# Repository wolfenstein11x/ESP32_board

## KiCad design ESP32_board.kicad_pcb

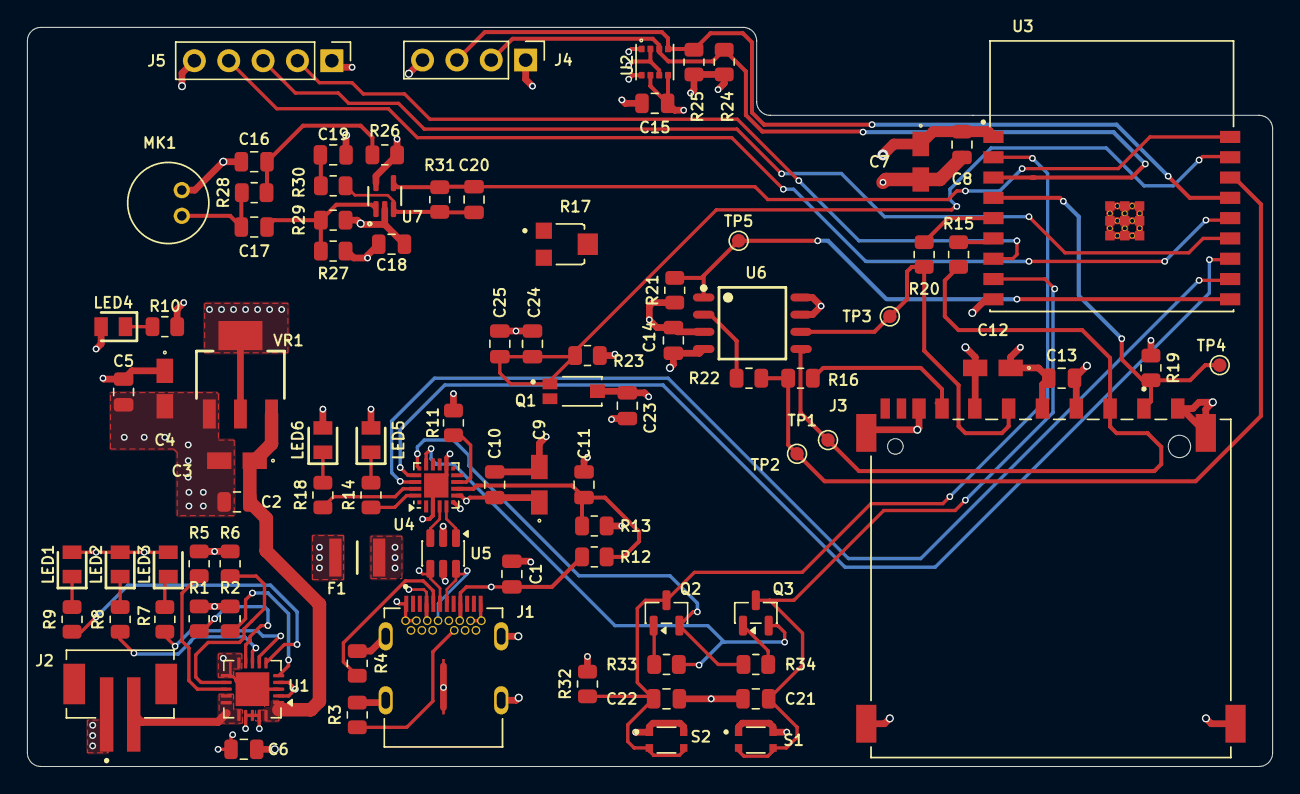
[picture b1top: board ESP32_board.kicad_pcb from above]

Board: 4 copper layers, 92.0 x 54.6 mm, 90 parts (0 on the bottom side), 58 nets.

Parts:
C1, C2, C5, C8, C10, C13, C14, C15, C16, C18, C20, C21, C23: 0.1u; C_0805_2012Metric
C3, C4, C7, C12: 10u; T491A
C6, C11, C19, C22: 1u; C_0805_2012Metric
C9: 4.7u; T491A
C17: 0.01u; C_0805_2012Metric
C24, C25: 10n; C_0805_2012Metric
F1: 0ZCH0110AF2E; FUSC3226X100N
J1: SS-52400-002; BELFUSE_SS-52400-002
J2: B2B-PH-SM4-TB; JST_B2B-PH-SM4-TB
J3: GSD090012SEU; AMPHENOL_GSD090012SEU
J4: Conn_01x04_Pin; PinHeader_1x04_P2.54mm_Vertical
J5: Conn_01x05_Pin; PinHeader_1x05_P2.54mm_Vertical
LED1, LED4, LED6: LTST-C170KRKT; LEDC2012X120N
LED2, LED5: LTST-C170GKT; LEDC2012X120N
LED3: LTST-C170TBKT; LEDC2012X120N
MK1: CMC-5042PF-AC; CUI_CMC-5042PF-AC
Q1: TEMT6000X01; TRANS_TEMT6000X01
Q2, Q3: BC817; SOT-23
R1, R2, R19, R21, R23, R30, R32, R33, R34: 10k; R_0805_2012Metric
R3, R4: 5.1k; R_0805_2012Metric
R5, R26, R28: 2k; R_0805_2012Metric
R6: 20k; R_0805_2012Metric
R7, R8, R9, R10, R14, R18: 470; R_0805_2012Metric
R11: 1k; R_0805_2012Metric
R12: 22.1k; R_0805_2012Metric
R13: 47.5k; R_0805_2012Metric
R15, R16, R20, R22: 50; R_0805_2012Metric
R17: 35WR100KLFTR; TRIM_35WR100KLFTR
R24, R25: 4.7k; R_0805_2012Metric
R27, R29: 1M; R_0805_2012Metric
R31: 100k; R_0805_2012Metric
S1: Boot Button; SW_USLPT2819DT2TR
S2: Reset Button; SW_USLPT2819DT2TR
TP1, TP2, TP3, TP4, TP5: TestPoint; TestPoint_Pad_D1.0mm
U1: MCP73871; QFN-20-1EP_4x4mm_P0.5mm_EP2.5x2.5mm
U2: BME280; PSON65P250X250X100-8N
U3: ESP32-C3-WROOM-02-H4; MODULE_ESP32-C3-WROOM-02-H4
U4: CP2102N-Axx-xQFN20; SiliconLabs_QFN-20-1EP_3x3mm_P0.5mm_EP1.8x1.8mm
U5: USBLC6-2SC6; SOT-23-6
U6: W25Q32JVSSIQ; SOIC127P790X216-8N
U7: MAX4466EXK; SOT65P210X110-5N
VR1: LM1117MPX-3.3; VREG_LM1117MPX-3.3

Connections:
+3V3: C4.1, C5.1, C7.1, C8.1, C9.1, C10.1, C12.1, C13.1, C14.1, C15.1, C18.1, C23.1, J3.4 (VDD1), J4.1, J5.1, LED4.2 (A), LED5.2 (A), LED6.2 (A), Q1.3, R11.1, R19.1, R21.1, R24.1, R25.1, R26.1, R27.1, R32.2, U2.2 (CSB), U2.6 (VDDIO), U2.8 (VDD), U3.1 (3V3), U4.6 (VDD), U4.7 (VREGIN), U6.3 (~WP(IO2)), U6.7 (~HOLD/~RESET(IO3)), U6.8 (VCC), U7.5 (VCC), VR1.2 (VOUT_2), VR1.4 (VOUT_4)
+5V: C2.1, C3.1, U1.1 (OUT), U1.20 (OUT), VR1.3 (VIN)
/+5V_USB: C6.1, F1.2, LED1.2 (A), LED2.2 (A), LED3.2 (A), U1.2 (VPCC), U1.4 (PROG2), U1.17 (CE), U1.18 (IN), U1.19 (IN)
/CC1: J1.A5 (CC1), R4.1
/CC2: J1.B5 (CC2), R3.1
/CHARGED: R8.1, U1.8 (STAT1/~LBO)
/CHARGING: R9.1, U1.6 (~PG)
/CHARGING_POWER_GOOD: R7.1, U1.7 (STAT2)
/ESP32-C3-02/BOOT: C21.1, Q3.3 (C), S1.3, S1.4, U3.8 (IO9)
/ESP32-C3-02/CS_SD: J3.1 (CD/DAT3), R19.2, TP4.1 (1_1), U3.4 (IO5)
/ESP32-C3-02/CS~: R21.2, TP5.1 (1_1), U3.10 (IO10), U6.1 (~CS)
/ESP32-C3-02/DTR: Q3.2 (E), R33.1, U4.15 (~CTS)
/ESP32-C3-02/EN: C22.1, Q2.3 (C), R32.1, S2.3, S2.4, U3.2 (EN)
/ESP32-C3-02/GPIO8: J5.2, U3.7 (IO8)
/ESP32-C3-02/GPIO18: J5.3, U3.13 (IO18)
/ESP32-C3-02/GPIO19: J5.4, U3.14 (IO19)
/ESP32-C3-02/MIC_OUT: C20.2, R31.2, U3.18 (IO0), U7.4 (OUT)
/ESP32-C3-02/MISO_DO: R16.2, R22.2, TP2.1 (1_1), U3.16 (IO2)
/ESP32-C3-02/MISO_DO_FLASH: R22.1, U6.2 (DO(IO1))
/ESP32-C3-02/MISO_DO_SD: J3.7 (DAT0), R16.1
/ESP32-C3-02/MOSI_DI: J3.2 (CMD), R15.2, TP1.1 (1_1), U6.5 (DI(IO0))
/ESP32-C3-02/MOSI_DI_ESP32: R15.1, U3.6 (IO7)
/ESP32-C3-02/PHOTO_C: C24.2, C25.2, Q1.1, R23.1, U3.17 (IO1)
/ESP32-C3-02/RTS: Q2.2 (E), R34.1, U4.16 (~RTS)
/ESP32-C3-02/RX_TX: U3.12 (TXD), U4.17 (RXD)
/ESP32-C3-02/SCL: J4.3, R25.2, U2.4 (SCK), U3.15 (IO3)
/ESP32-C3-02/SCLK: J3.5 (CLK), R20.1, TP3.1 (1_1), U6.6 (CLK)
/ESP32-C3-02/SCLK_ESP32: R20.2, U3.5 (IO6)
/ESP32-C3-02/SDA: J4.2, R24.2, U2.3 (SDI), U3.3 (IO4)
/ESP32-C3-02/Sensors/PREAMP_IN+: C17.2, R27.2, R29.1, U7.1 (IN+)
/ESP32-C3-02/Sensors/PREAMP_IN-: C20.1, R30.1, R31.1, U7.3 (IN-)
/ESP32-C3-02/TX_RX: U3.11 (RXD), U4.18 (TXD)
/ESP32-C3-02/USB_D+: U4.4 (D+), U5.3 (I/O2)
/ESP32-C3-02/USB_D-: U4.5 (D-), U5.1 (I/O1)
/PROG1: R5.1, U1.13 (PROG1)
/PROG3: R6.1, U1.12 (PROG3)
/PWR_LED: LED4.1 (K), R10.2
/TE~: R1.1, U1.9 (~TE)
/THERM: R2.1, U1.5 (THERM)
/USB_DN: J1.A7 (DN1), J1.B7 (DN2), U5.6 (I/O1)
/USB_DP: J1.A6 (DP1), J1.B6 (DP2), U5.4 (I/O2)
/VBAT: J2.2, U1.14 (V_{BAT}), U1.15 (V_{BAT}), U1.16 (V_{BAT_SENSE})
/VBUS: C1.1, F1.1, J1.A4 (VBUSA1), J1.A9 (VBUSA2), J1.B4 (VBUSB1), J1.B9 (VBUSB2), R12.1, U5.5 (VBUS)
GND: C1.2, C2.2, C3.2, C4.2, C5.2, C6.2, C7.2, C8.2, C9.2, C10.2, C11.2, C12.2, C13.2, C14.2, C15.2, C16.1, C18.2, C19.1, C21.2, C22.2, C23.2, C24.1, C25.1, J1.A1 (GNDA1), J1.A12 (GNDA2), J1.B1 (GNDB1), J1.B12 (GNDB2), J1.G1 (GND/SHIELD), J1.G2 (GND/SHIELD), J1.G3 (GND/SHIELD), J1.G4 (GND/SHIELD), J1.S1 (GND/SHIELD), J1.S2 (GND/SHIELD), J1.S3 (GND/SHIELD), J1.S4 (GND/SHIELD), J2.1, J3.3 (VSS1), J3.6 (VSS2), J3.8 (DAT1), J3.9 (DAT2), J3.G1 (SHIELD_GND), J3.G2 (SHIELD_GND), J3.G3 (SHIELD_GND), J3.G4 (SHIELD_GND), J4.4, J5.5, MK1.GND, R1.2, R2.2, R3.2, R4.2, R5.2, R6.2, R10.1, R13.2, R23.2, R29.2, S1.1, S1.2, S2.1, S2.2, U1.3 (SEL), U1.10 (V_{SS}), U1.11 (V_{SS}), U1.21 (V_{SS}), U2.1 (GND), U2.5 (SDO), U2.7 (GND), U3.9 (GND), U3.19 (GND), U3.20 (GND), U3.21 (GND), U3.22 (GND), U3.23 (GND), U3.24 (GND), U3.25 (GND), U3.26 (GND), U3.27 (GND), U3.28 (GND), U3.29 (GND), U3.30 (GND), U3.31 (GND), U3.32 (GND), U3.33 (GND), U3.34 (GND), U3.35 (GND), U3.36 (GND), U3.37 (GND), U3.38 (GND), U3.39 (GND), U4.3 (GND), U4.12 (GND), U4.21 (GND), U5.2 (GND), U6.4 (GND), U7.2 (GND), VR1.1 (GND)
unnamed: C16.2, R26.2, R28.1
unnamed: C17.1, MK1.OUT, R28.2
unnamed: C19.2, R30.2
unnamed: LED1.1 (K), R9.2
unnamed: LED2.1 (K), R8.2
unnamed: LED3.1 (K), R7.2
unnamed: LED5.1 (K), R14.2
unnamed: LED6.1 (K), R18.2
unnamed: Q2.1 (B), R33.2
unnamed: Q3.1 (B), R34.2
unnamed: C11.1, R12.2, R13.1, U4.8 (VBUS)
unnamed: R11.2, U4.9 (~RST)
unnamed: R18.1, U4.19 (~RXT/GPIO.3)
unnamed: R14.1, U4.20 (~TXT/GPIO.2)
